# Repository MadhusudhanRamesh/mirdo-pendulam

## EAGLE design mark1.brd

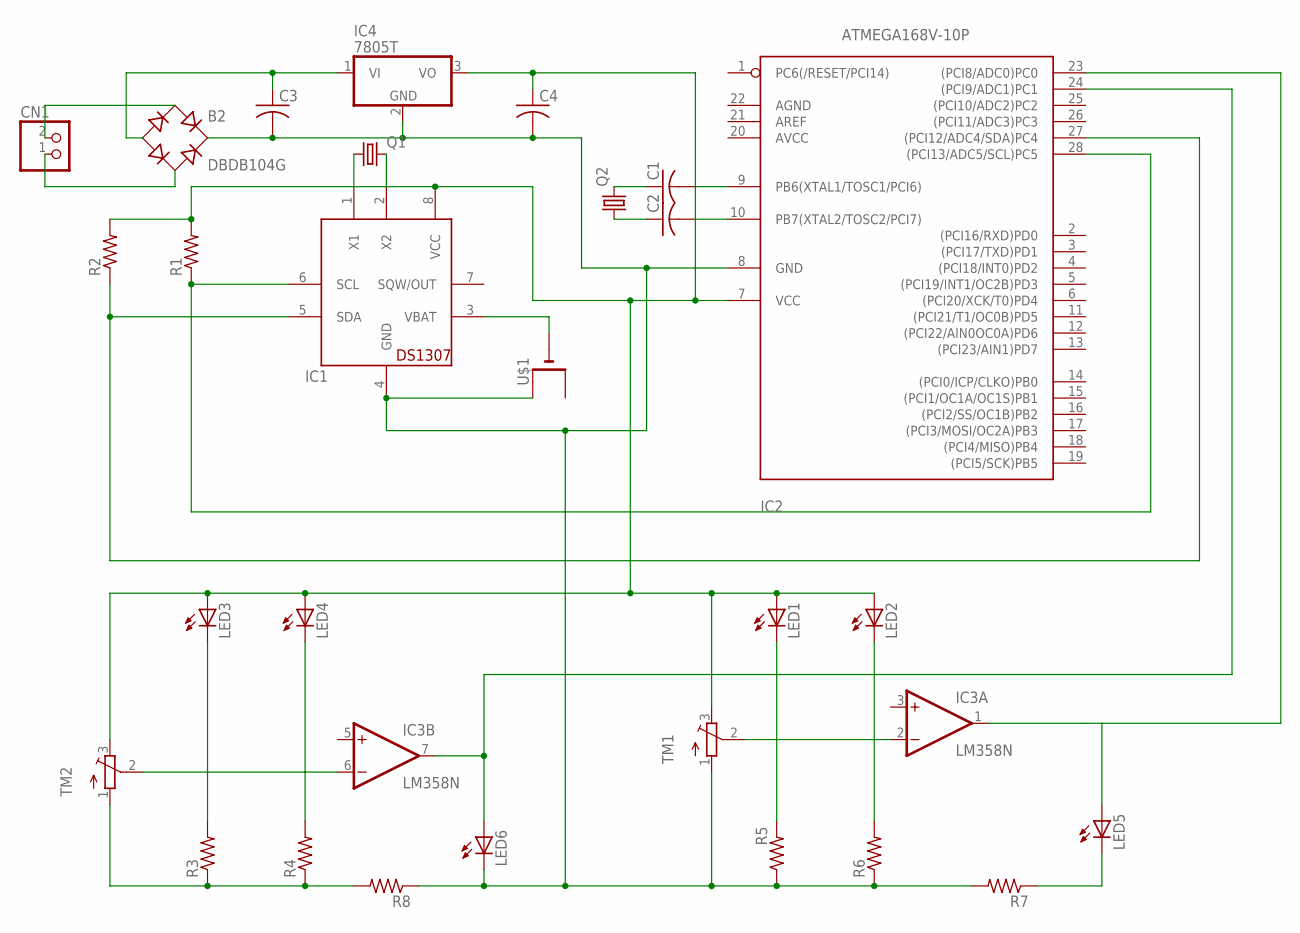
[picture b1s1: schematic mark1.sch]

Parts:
B2: DBDB104G; DB
C1, C2, C3, C4: C-US025-024X044; C025-024X044
CN1: JST_2PIN-THM; JST-PH-2-THM
IC1: DS1307; DIL08
IC2: ATMEGA168V-10P; DIL28-3
IC3: LM358N; DIL08
IC4: 7805T; TO220H
LED1, LED2, LED3, LED4, LED5, LED6: LED5MM
Q1: CRYSTALTC26V; TC26V
Q2: CRYSTALHC33U-V; HC33U-V
R1, R2, R3, R4, R5, R6, R7, R8: R-US_0204/7; 0204/7
TM1, TM2: TRIMPOT3386; TRIM-3386
U$1: CR1220THM; CR1220-THM

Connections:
unnamed: IC1.5 (SDA), IC2.27 ((PCI12/ADC4/SDA)PC4), R2.1
unnamed: IC1.6 (SCL), IC2.28 ((PCI13/ADC5/SCL)PC5), R1.1
unnamed: IC1.1 (X1), Q1.1
unnamed: IC1.2 (X2), Q1.2
unnamed: IC1.3 (VBAT), U$1.-
unnamed: B2.-, C3.1, IC4.1 (VI)
unnamed: C1.2, IC2.9 (PB6(XTAL1/TOSC1/PCI6))
unnamed: C1.1, Q2.2
unnamed: C2.1, Q2.1
unnamed: C2.2, IC2.10 (PB7(XTAL2/TOSC2/PCI7))
unnamed: IC3.6 (-IN), TM2.2 (S)
unnamed: IC3.2 (-IN), TM1.2 (S)
unnamed: LED3.K (C), R3.2
unnamed: LED4.K (C), R4.2
unnamed: LED1.K (C), R5.2
unnamed: LED2.K (C), R6.2
unnamed: IC2.24 ((PCI9/ADC1)PC1), IC3.7 (OUT), LED6.A
unnamed: R3.1, R4.1, R8.2, TM2.1 (A)
unnamed: B2.+, C3.2, C4.2, IC1.4 (GND), IC2.8 (GND), IC4.2 (GND), LED6.K (C), R5.1, R6.1, R7.2, R8.1, TM1.1 (A), U$1.+1 (+)
unnamed: IC2.23 ((PCI8/ADC0)PC0), IC3.1 (OUT), LED5.A
unnamed: LED5.K (C), R7.1
unnamed: C4.1, IC1.8 (VCC), IC2.7 (VCC), IC4.3 (VO), LED1.A, LED2.A, LED3.A, LED4.A, R1.2, R2.2, TM1.3 (E), TM2.3 (E)
unnamed: B2.AC1, CN1.2 (1)
unnamed: B2.AC2, CN1.1 (2)
V+: IC3.8 (V+)
V-: IC3.4 (V-)

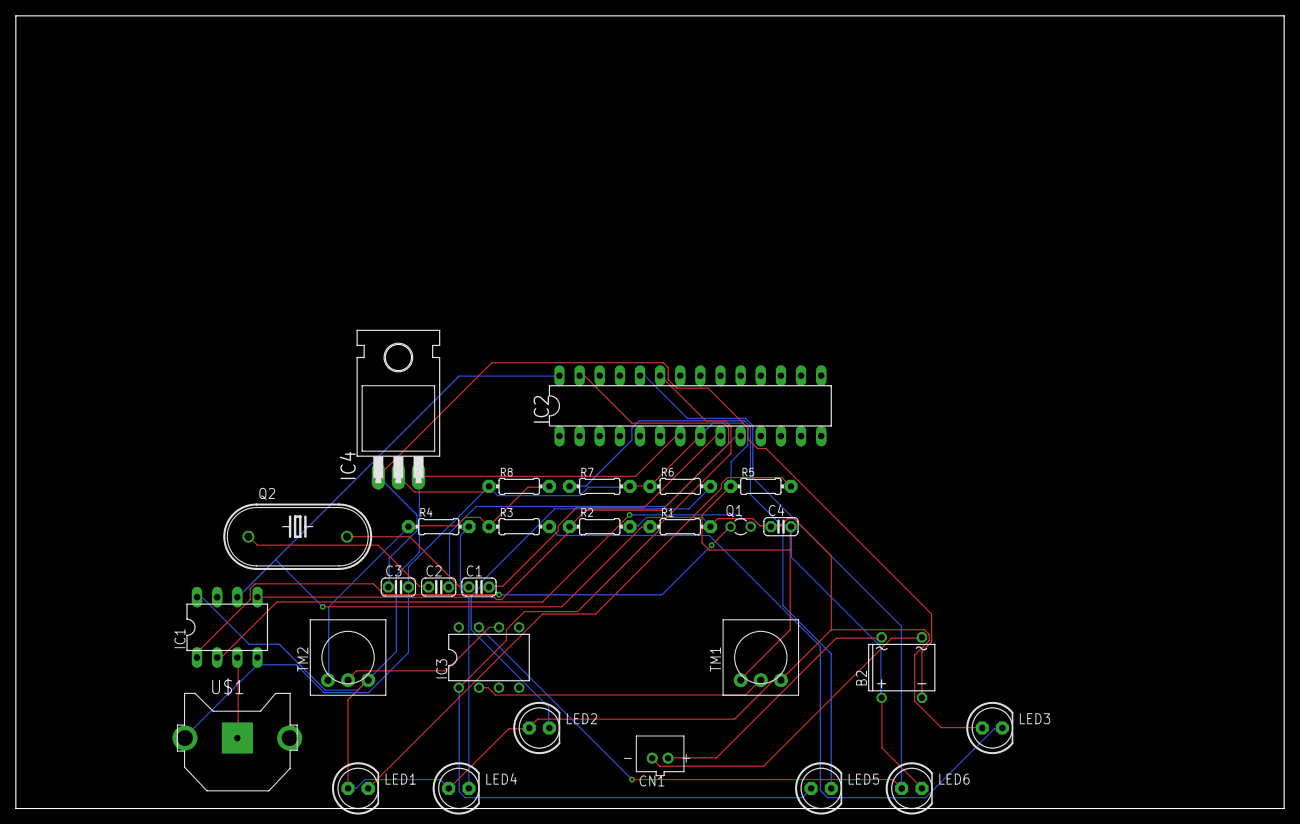
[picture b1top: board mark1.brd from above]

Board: 2 copper layers, 160.0 x 100.0 mm, 29 parts (0 on the bottom side), 24 nets.

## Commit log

2022-01-07 schematics and pcb
